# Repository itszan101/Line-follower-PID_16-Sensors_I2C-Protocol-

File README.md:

# Line-follower-PID_16-Sensors_I2C-Protocol-

This is a personal project that i made for college assignment, i make a Line-Follower robot with spesific feature.
- Implementing 16 Sensors (Photodiode, resistor, and led)
- PID calculation to help robot run smoothly, and recogize obstacle route and intersection.
- Multiplexer x16 Modul for arduino atmega 328

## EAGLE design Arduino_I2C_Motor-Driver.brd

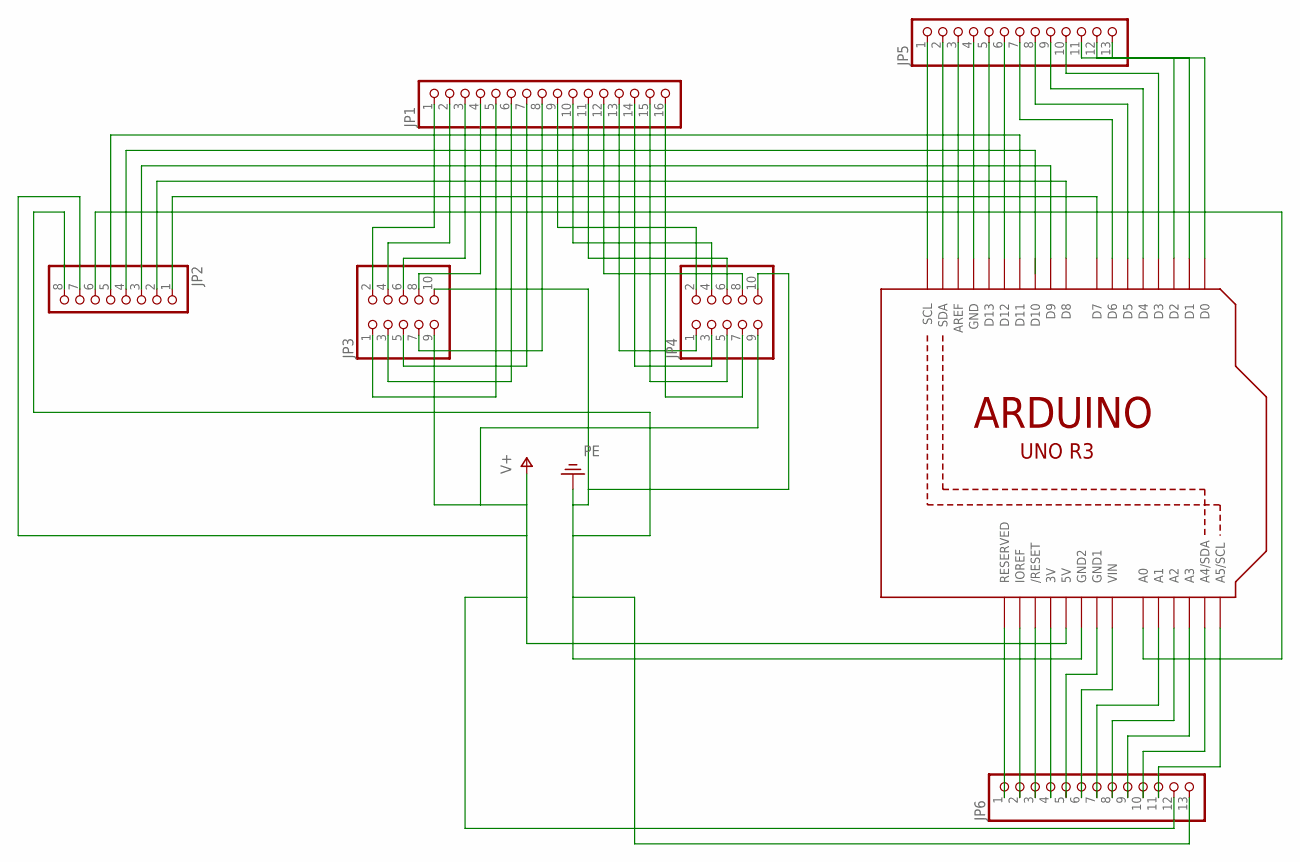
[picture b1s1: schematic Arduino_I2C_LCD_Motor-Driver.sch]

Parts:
JP1: PINHD-1X16; 1X16
JP2: PINHD-1X8; 1X08
JP3, JP4: PINHD-2X5; 2X05
JP5, JP6: PINHD-1X13; 1X13
U1: ARDUINOR3-BPLACE

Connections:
unnamed: JP2.2, U1.D8
unnamed: JP2.3, U1.D9
unnamed: JP2.1, U1.D7
unnamed: JP2.5, U1.D11
unnamed: JP1.1, JP3.2
unnamed: JP1.2, JP3.4
unnamed: JP2.6, U1.A0
unnamed: JP1.3, JP3.6
unnamed: JP1.4, JP3.8
unnamed: JP1.5, JP3.1
unnamed: JP1.6, JP3.3
unnamed: JP1.7, JP3.5
unnamed: JP1.8, JP3.7
unnamed: JP1.9, JP4.2
unnamed: JP1.10, JP4.4
unnamed: JP1.11, JP4.6
unnamed: JP1.12, JP4.8
unnamed: JP1.13, JP4.1
unnamed: JP1.14, JP4.3
unnamed: JP1.15, JP4.5
unnamed: JP1.16, JP4.7
unnamed: JP5.1, U1.SCL
unnamed: JP5.2, U1.SDA
unnamed: JP5.3, U1.AREF
unnamed: JP5.4, U1.GND
unnamed: JP5.5, U1.D13
unnamed: JP5.6, U1.D12
unnamed: JP5.7, U1.D6
unnamed: JP5.8, U1.D5
unnamed: JP5.9, U1.D4
unnamed: JP5.10, U1.D3
unnamed: JP5.11, U1.D2
unnamed: JP5.12, U1.D1
unnamed: JP5.13, U1.D0
unnamed: JP6.1, U1.RESERVED
unnamed: JP6.2, U1.IOREF
unnamed: JP6.3, U1.RESET (/RESET)
unnamed: JP6.4, U1.3V
unnamed: JP6.5, U1.GND1
unnamed: JP6.6, U1.VIN
unnamed: JP6.7, U1.A1
unnamed: JP6.8, U1.A2
unnamed: JP6.9, U1.A3
unnamed: JP6.10, U1.A4 (A4/SDA)
unnamed: JP6.11, U1.A5 (A5/SCL)
PE: JP2.8, JP3.10, JP4.10, JP6.13, U1.GND2
V+: JP2.7, JP3.9, JP4.9, JP6.12, U1.5V

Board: 2 copper layers, 7 parts (0 on the bottom side), 47 nets, no tracks yet.

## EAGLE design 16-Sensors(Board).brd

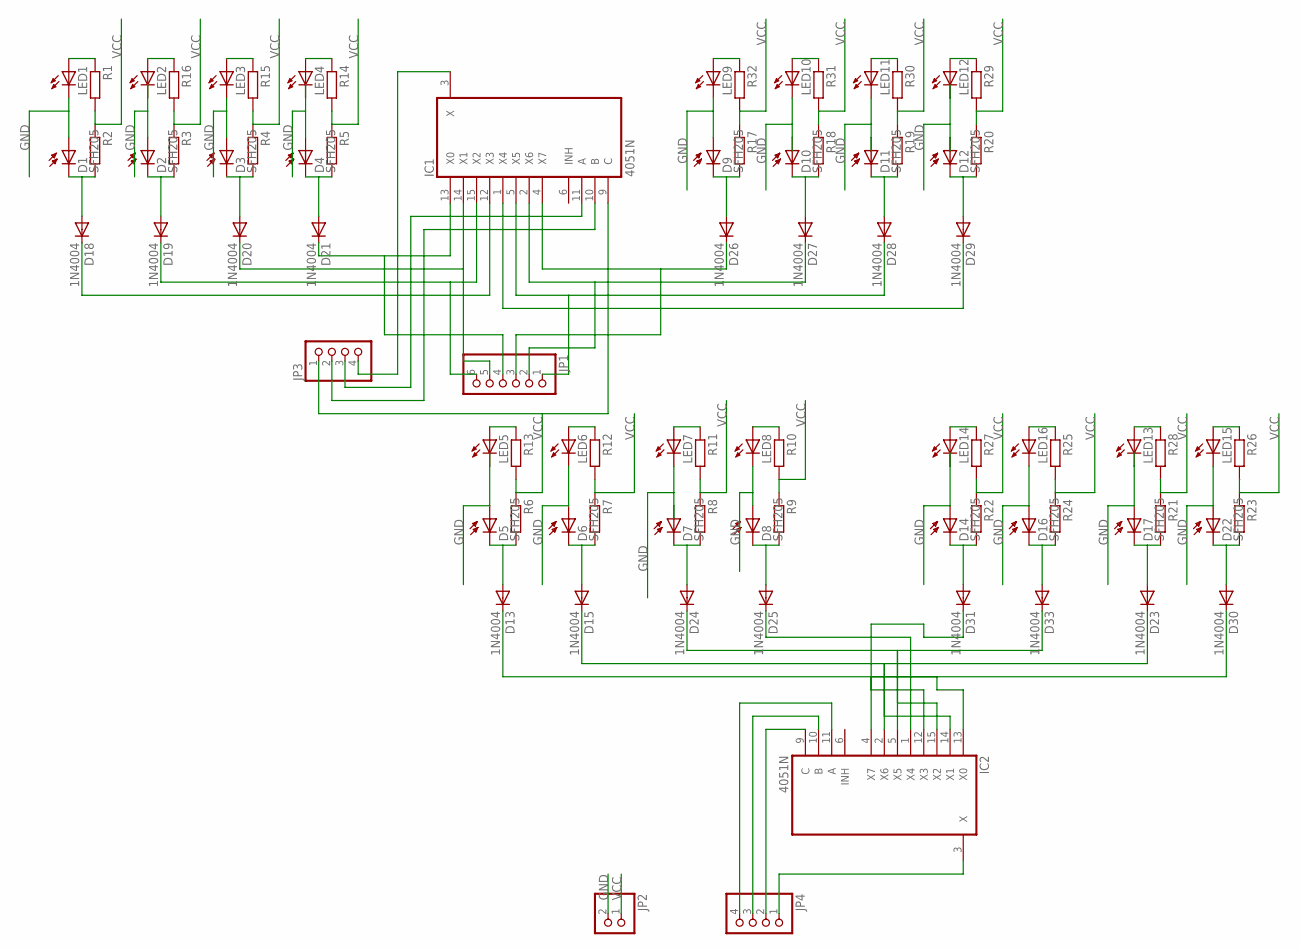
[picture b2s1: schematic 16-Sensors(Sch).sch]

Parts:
D1, D2, D3, D4, D5, D6, D7, D8, D9, D10, D11, D12, D14, D16, D17, D22: SFH205
D13, D15, D18, D19, D20, D21, D23, D24, D25, D26, D27, D28, D29, D30, D31, D33: 1N4004; DO41-10
IC1, IC2: 4051N; DIL16
JP1: PINHD-1X6; 1X06
JP2: PINHD-1X2; 1X02
JP3, JP4: PINHD-1X4; 1X04
LED1, LED2, LED3, LED4, LED5, LED6, LED7, LED8, LED9, LED10, LED11, LED12, LED13, LED14, LED15, LED16: LED5MM
R1, R2, R3, R4, R5, R6, R7, R8, R9, R10, R11, R12, R13, R14, R15, R16, R17, R18, R19, R20, R21, R22, R23, R24, R25, R26, R27, R28, R29, R30, R31, R32: R-EU_0204/5; 0204/5

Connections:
GND: D1.A, D2.A, D3.A, D4.A, D5.A, D6.A, D7.A, D8.A, D9.A, D10.A, D11.A, D12.A, D14.A, D16.A, D17.A, D22.A, IC1.8 (GND), IC2.8 (GND), JP2.2, LED1.K (C), LED2.K (C), LED3.K (C), LED4.K (C), LED5.K (C), LED6.K (C), LED7.K (C), LED8.K (C), LED9.K (C), LED10.K (C), LED11.K (C), LED12.K (C), LED13.K (C), LED14.K (C), LED15.K (C), LED16.K (C)
unnamed: LED9.A, R32.1
unnamed: LED10.A, R31.1
unnamed: LED11.A, R30.1
unnamed: LED12.A, R29.1
unnamed: D26.C, IC1.4 (X7), JP1.3
unnamed: LED14.A, R27.1
unnamed: D21.C, IC1.13 (X0), JP1.4
unnamed: D20.C, IC1.14 (X1), JP1.5
unnamed: LED1.A, R1.1
unnamed: LED2.A, R16.1
unnamed: LED3.A, R15.1
unnamed: LED4.A, R14.1
unnamed: D27.C, IC1.2 (X6), JP1.2
unnamed: D19.C, IC1.15 (X2), JP1.6
unnamed: D18.C, IC1.12 (X3)
unnamed: D28.C, IC1.5 (X5), JP1.1
unnamed: D3.K (C), D20.A, R4.2
unnamed: IC1.3 (X), JP3.4
unnamed: D29.C, IC1.1 (X4)
unnamed: IC1.11 (A), JP3.3
unnamed: IC1.10 (B), JP3.2
unnamed: LED5.A, R13.1
unnamed: IC1.9 (C), JP3.1
unnamed: LED7.A, R11.1
unnamed: LED8.A, R10.1
unnamed: D5.K (C), D13.A, R6.2
unnamed: D6.K (C), D15.A, R7.2
unnamed: LED6.A, R12.1
unnamed: LED13.A, R28.1
unnamed: D17.K (C), D23.A, R21.2
unnamed: D16.K (C), D33.A, R24.2
unnamed: D22.K (C), D30.A, R23.2
unnamed: LED15.A, R26.1
unnamed: D31.C, IC2.1 (X4)
unnamed: D33.C, IC2.5 (X5)
unnamed: D30.C, IC2.4 (X7)
unnamed: D25.C, IC2.12 (X3)
unnamed: D24.C, IC2.15 (X2)
unnamed: D15.C, IC2.14 (X1)
unnamed: D13.C, IC2.13 (X0)
unnamed: IC2.3 (X), JP4.1
unnamed: IC2.9 (C), JP4.2
unnamed: IC2.10 (B), JP4.3
unnamed: IC2.11 (A), JP4.4
unnamed: D1.K (C), D18.A, R2.2
unnamed: D2.K (C), D19.A, R3.2
unnamed: D23.C, IC2.2 (X6)
unnamed: D4.K (C), D21.A, R5.2
unnamed: D7.K (C), D24.A, R8.2
unnamed: D8.K (C), D25.A, R9.2
unnamed: D9.K (C), D26.A, R17.2
unnamed: D10.K (C), D27.A, R18.2
unnamed: D11.K (C), D28.A, R19.2
unnamed: D12.K (C), D29.A, R20.2
unnamed: D14.K (C), D31.A, R22.2
unnamed: LED16.A, R25.1
VCC: IC1.16 (VCC), IC2.16 (VCC), JP2.1, R1.2, R2.1, R3.1, R4.1, R5.1, R6.1, R7.1, R8.1, R9.1, R10.2, R11.2, R12.2, R13.2, R14.2, R15.2, R16.2, R17.1, R18.1, R19.1, R20.1, R21.1, R22.1, R23.1, R24.1, R25.2, R26.2, R27.2, R28.2, R29.2, R30.2, R31.2, R32.2
VEE: IC1.7 (VEE), IC2.7 (VEE)

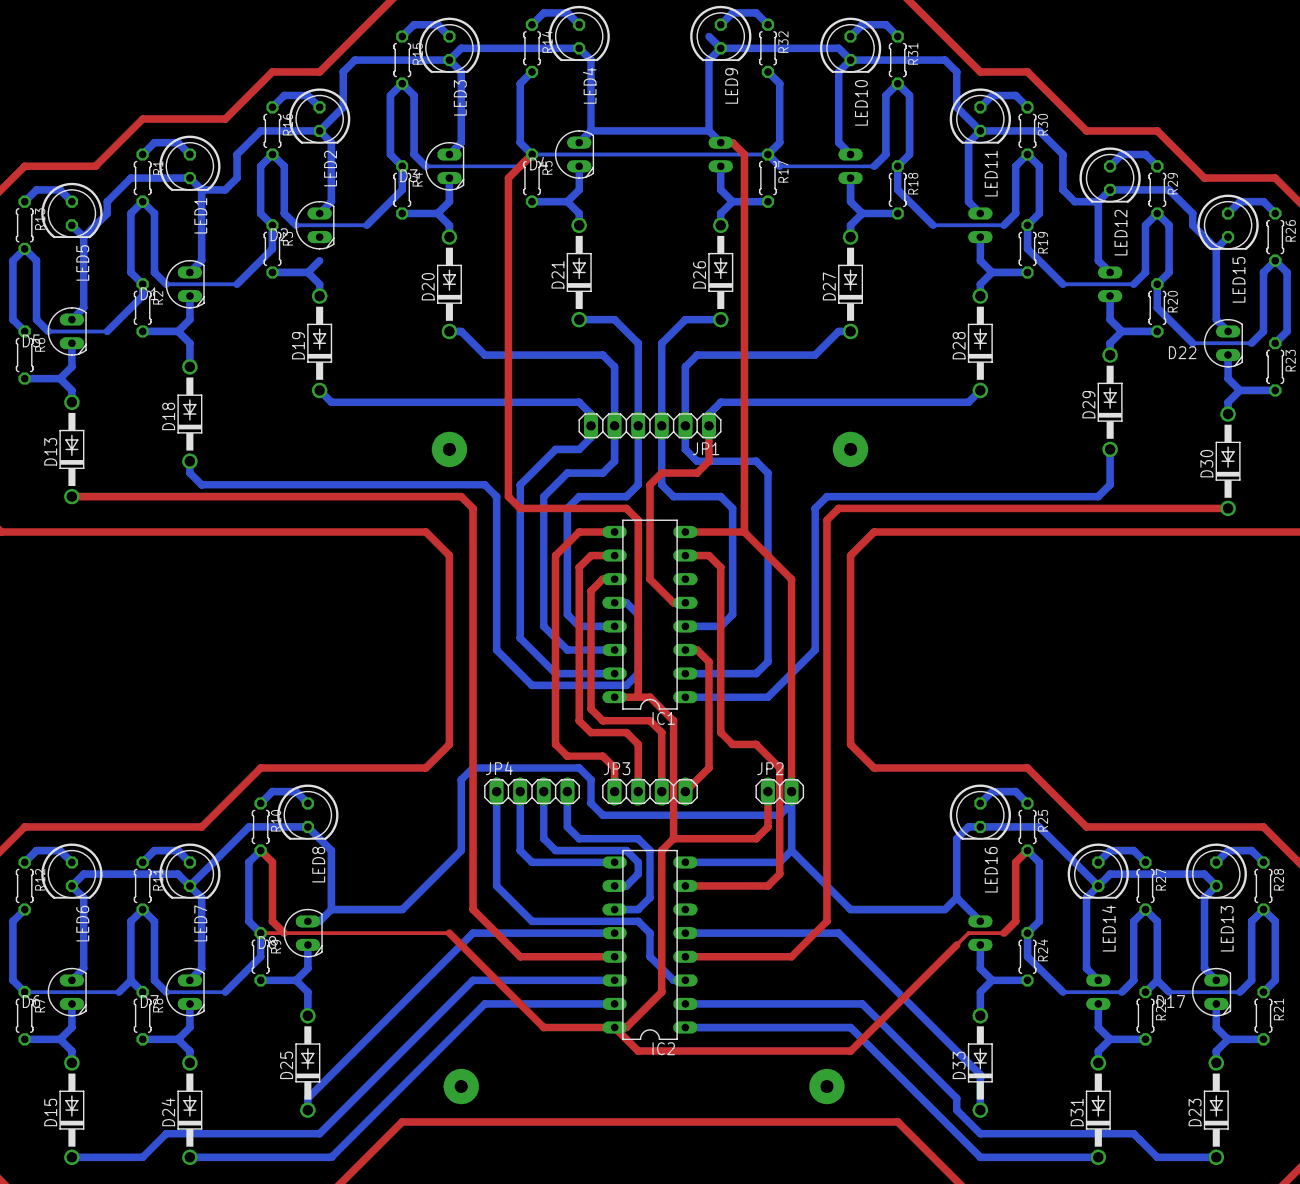
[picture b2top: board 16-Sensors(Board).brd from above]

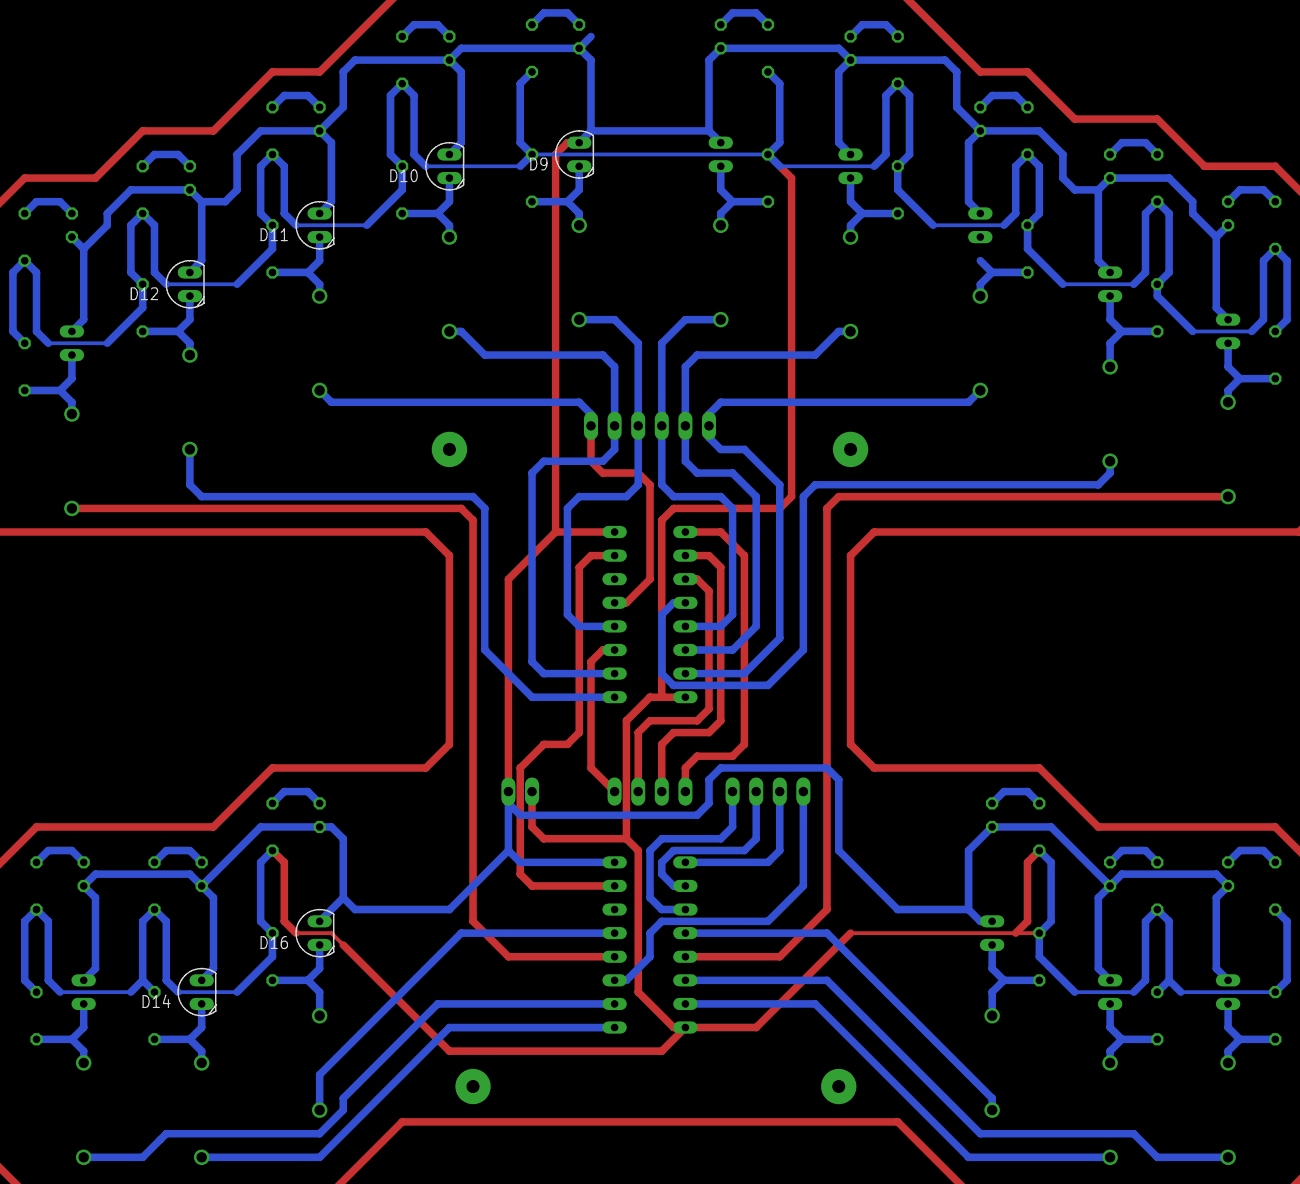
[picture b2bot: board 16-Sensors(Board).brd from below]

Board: 2 copper layers, 86 parts (6 on the bottom side), 59 nets.
